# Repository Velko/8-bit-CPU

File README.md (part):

8-bit-CPU
=========

After watching [series of videos][eater-net-8bit] by Ben Eater building an 8-bit computer from scratch,
I was hooked. Various thoughts for improvements and experiments was running through my mind. But first
I have to build one. Improvements will come later. Whom am I kidding? I'll never be able to build an
exact replica, I'll incorporate improvements as I go.

In contrast to Ben, I'm not that crazy about building the whole thing on breadboards. PCBs are fine,
I like them, but building the whole thing on single board takes away the flexibility. So the plan is
to make a small board for each module and connect them together.

I plan to build a prototype module on breadboard, play around with it and then design and make a PCB
for it. It might also be interesting to make the boards little customizable (leave a chip out, create
a solder bridge, use shorter connector) so that they can be re-used for different purposes.

Of course, some parts of it might stay on a breadboard forever, or I might choose to create PCBs for
those as well. I don't know, time will tell. But the main idea is that it should be possible to swap
out PCBs for breadboards and vice versa.

Key differences from Ben's version
==================================

256 bytes of memory
-------------------

I felt that 16 bytes of total memory might be too tight, went for 8-bit addressing and 256 bytes
of memory straight from the beginning. "Real" 32 KiB SRAM chip is used, with remaining higher address
lines tied to ground. Expanding to 256 bytes does not introduce more complexity, I think that it even
made things easier. The emulated version has (and is able to use) 64KiB of memory, hardware version
has not catched up with it yet.

ROM and bootloader mode
-----------------------

I was not in the mood for _any_ DIP switch toggling for program entry, so I added an EEPROM instead.
Still I did not want to go full Harvard architecture with separate program and data memories, so
there's bootloader mode instead.

To enable it, RAM's Chip Enable is connected together with Write Enable, while ROM's Chip Enable is
connected with Output Enable of the RAM. What happens is that all reads comes from ROM and all writes
goes into RAM.

I have bootloader code in the beginning of the program that copies contents of all 256 bytes into RAM
and then patches itself (in RAM) to be skipped. It is nice to have more memory, since in original
version there are only 16 bytes total, but I can afford to _waste_ similar amount on bootloader.

In _run mode_ ROM's Chip Enable is tied to disabled state permanently, while RAM is permanently enabled.

4 flags
-------

In addition to Z and C flags, there are Negative and oVerflow flags. Took an inspiration from
[AVR Instruction Set Manual][avr-instructions], on how to implement various branching instructions.
N and V flags are required for some. N bit is just a copy of 7-th bit of the result. oVerflow indicates
that the sign bit "overflowed" as a result of addition/subtraction. In short it can be defined as:
*If sign bits of both addition operands are equal, but sign bit of the result is different, the overflow
occured.*

C flag got an additional update to act as a Borrow bit in subtraction. It behaves same way as in
Z80 / AVR / x86 processors. In subtraction the meaning of C is opposite from 6502 or Ben's version,
I find this more intuitive.

256 opcodes
-----------

As memory was expanded to 256 bytes, it was not possible to encode opcode and address in single byte
anymore. Instructions may require multiple bytes anyway now. Instruction Register loads 8-bit opcode and
extra arguments are fetched from RAM when needed, there's room for 256 opcodes.

However, number of opcodes is also limited by capacity of control EEPROMs. 8 bits for opcode + 4 bits
for flags + 3 bits for instruction step = 15 address lines. This calls for 32K EEPROM - 28C256. They
felt a little pricey when I ordered parts and I was not completely sure if I'll really need them. For
now I only have 28C64 chips, limiting number of opcodes to 64. It is still 4 times more than in Ben's
version.

There are plans to support "extended" opcodes (up to 512, or even more, if required). Planning to switch
to SST39SF010A chips for microcode ROMs. These have more capacity (and address lines) and are a bit
cheaper as well.

Modular ALU
-----------

Currently there are 2 ALU modules: Add/Subtract (with or without carry/borrow),
and AND/OR. 2 more modules are about to come - XOR/NOT, Shift/Nibble-swap.

Flags register as an independent entity
---------------------------------------

Zero flag's calculation takes input from the Bus, instead of being embedded in ALU module. This allows
to add additional ALU modules and keep just one instance of Z calculation circuitry. Additionally, it
is possible to calculate flags for anything on the Bus, for example - while loading byte from memory.
There's additional function for flags register to be sent and loaded from bus directly. Currently
there is no use for that, but it may become handy if flags need to be saved and restored for some reason
(perhaps, to implement interrupts).

Double-latching registers
-------------------------

One of the main sources of instability in Ben's design is that registers' "tap outputs" (ones that
connects registers to ALU, RAM or Control Logic) change immediately when new value is latched.
This is especially important with Flags and Instruction Register, as it creates the infamous
"EEPROM noise" on the rising clock edge, when it can cause unexpected effects. It might not be such
an issue for general-purpose registers or MAR, but it is better that everything holds steady while
the clock line is high.

The double-latching technique adds additional D flip-flops between register's primary ones and its
"tap output". These additional flip-flops are configured to latch on the inverted clock, therefore
output stays unchanged until the falling edge.

Dual-output registers
---------------------

General purpose registers got dual 3-state "tap outputs". Instead of ALU inputs being hardwired to
registers A and B, now (with appropriate control signals) it is possible to connect them differently,
for example do A + A directly. It also allows additional registers (C and D), that could be used
with ALU directly. Currently this feature is not used and control lines are wired for steady "on",
but the potential is there.

Quarter-clock
-------------

One of the sources of instability in Ben's version is RC-circuit used as an edge detector in RAM
module. A common technique is to isolate the circuit using extra logic gates, so that it does not
send spikes back in clock line. I, however, decided to eliminate the need for edge detection
completely. The thing with RAM is that it will keep loading the value all the time while Write Enable
line is enabled. If inputs change, the last value will be stored, which may not be one we want if
Write Enable is disabled on same moment as other control lines starts to change. Ben solved it using
edge detector circuit, I went in another direction and introduced a "dead time" between moment when
primary clock line goes low and inverted clock rises.

Added a counter (could have been anything that can divide the frequency) and few NOR gates on the
*clock module* I generate two 25% duty-cycle clock signals, that are offset by half of the cycle. It
looks like this:

Part of the cycle when both clocks are low ensures that RAM's Write Enable is not active when control
lines or bus changes.

While it is required only by RAM module, I see no downsides for using it globally (it might be an issue
at high clock frequencies, though). Also, now other un-clocked parts (e.g. 193 counter for Stack Pointer)
can be introduced without worries.

Muxed control lines
-------------------

A great way to save bits in Control EEPROMs is to add demultiplexers, which activates just a single line
from several. For example, by using 74*138 demultiplexer one can expand 3 bits to 7 control lines
(technically - to 8, but you need to reserve one as "unused"). Currently there are 2 demultiplexers
used - for OUT and for LOAD lines. For OUT it also prevents "invalid" conditions, such as multiple
modules trying to output value on the bus.

While, in theory, there might be need to load same value into multiple modules simultaneously, I've
not yet encountered one, and I'm happy to live with that limitation.

No MAR, separate Address Bus
----------------------------

While trying to adjust the architecture for 16-bit memory space, I found out that having a single
Main Bus and Memory Address Register comes with performance penalty, as all address transfers takes
more cycles.

After some experimentation I found out that the most optimal solution is to remove the MAR entirely
and have a separate 16-bit Address Bus, connected directly to the RAM chip(s).

Now, for example, Progam Counter can put an address on this bus, and the data is available to be sent on the
Main Bus.

Additionally, I re-designed PC in a way, that it can output the "old" value on the Address Bus, and
increment itself simultaneously. As a result, I can reduce the fetch stage of each instruction to just
single cycle.

There are some situations (like JMP instruction), when data should be exchanged between Address and
Main buses. There's a pair of special Transfer Registers, that allows to transfer low or high bytes
between the buses.

Arduino + Python test module
----------------------------

It started with hooking up an Arduino (on its own at first, then expanded output with 595 shift registers,
expanded even more with 139 demultiplexers and finally added 165 for expanded input) and writing some
sketches to verify if modules work as expected. Soon I realized that the environment is a bit limited
and while it can prove that everything works, it is not very helpful for diagnostics.

Reducing the functions of Arduino to "set control lines", "put to bus", "read from bus", "read flags",
"pulse a clock", etc. and implementing higher level logic in Python, makes it more flexible and quicker
to develop. Wrote a "client" that uses interactive input for diagnostics.

Started to implement Python functions that acts as an assembly instructions - for example: add(A, B)
switches all control lines and issues clock ticks as needed for the addition operation. Basically -
implemented microcode in Python. Later, with refactoring it became my main microcode definition and
is used as primary source for microcode EEPROM contents.

Using the instruction-like functions and [pytest][pytest] framework wrote a quite thorough test suite.
It can check couple hundred scenarios in just few seconds and point out if something does not work as
expected. It has already saved me several times, when I did some rewiring.

At the moment the test module is swapped out for "real" EEPROM-based Control Logic, but I'll definitely
find a way to use both of them in parallel, as it is too useful to be retired.

Programmed using CustomAsm
--------------------------

There was Python-based "assembler" at first, but in the end I adopted [CustomAsm][customasm] for
machine code generation. There's an utility that takes my microcode definition and exports a file,
describing them for [CustomAsm][customasm]. It takes it from there.

Debugger & IDE
--------------
As the Test module allows great deal of flexibility, I was able to also develop a simple debugger.
It can examine registers, RAM contents, single step. Addition of BRK instruction and corresponding
control line introduced ability to set breakpoints and run the program in full-speed. Unfortunately
it only works with emulator, as current hardware doesn't support both "normal" Control Logic and
Test modules connected simultaneously.

Later I went even further and developed a simple IDE, that allows basic code editing, integrates
with [CustomAsm][customasm] for compilation and has basic debugging functionality. One can single-step,
set breakpoints, examine registers. The IDE is far from polished experience, still it is useful.

Side-projects: EEPROM and Flash writers
---------------------------------------

As side projects, there are 2 boards (Arduino Uno shields), firmware and client utility for
programming DIP-28 and PLCC-32 EEPROMs (AT28C64 and AT28C256), as well as PLCC-32 Multi-Purpose
Flash (SST39SF*).

EEPROM board has additional headers, giving access to address and data pins, allowing the board to
act as a Test module, when connected to the Main Bus and control lines.

File upload and download uses XMODEM protocol, can be used with any terminal emulator. There's also
a (*nix-only) command-line client utility for convenience.

Emulated in Verilog
-------------------

In order to be able to work with the software side of the project, when hardware was not available,
I wrote an in-Arduino emulator, that speaks same protocol as Test module. With time that proved to
be insufficient, as Arduino was still needed, so I ported the C++ code to run on PC. It worked fine,
but was a hand-crafted approximation of the CPU, so I could not really test all "what if" scenarios
I'd like to.

So I decided to build another emulator, using proper hardware description language - [Verilog][verilog].
The idea was that I first make "building blocks" - (hopefully accurate) implementations of 74-series
logic chips, and then connect them together into CPU modules. This way I get a runnable representation
of the thing, how it should be built with real chips.

To provide connectivity with (virtualized) serial port, I built additional [VPI][vpi] module.

Repository index
================

* **.github** - configuration files for GitHub integration, e.g. workflows for GitHub Actions
* **.vscode** - configuration for Visual Studio Code
* **arduino** - Arduino sketches and C++ code, to help test and automate things
    * **bouncyy** - software button debouncer and "rebouncer"
    * **pincontrol** - substitute Control Logic. Controlled via serial link from **pycontrol**
    * **xmprog** - EEPROM/Flash programmer, file upload using XMODEM protocol
* **demo** - demo programs
* **doc** - some (mostly outdated) design thoughts, BOM, etc.
* **emulator** - hardware emulator in Verilog
    * **chips** - Verilog descriptions of (mostly 74xx) chips
    * **cpu-modules** - "wired up" CPU modules
    * **tests** - test benches for chips and modules
    * **vm** - a "virtual machine". Speaks same protocol as **pincontrol**
* **hardware** - hardware schematics, boards, etc.
    * **breadboard** - Fritzig projects for some modules
    * **pcb** - KiCad schematics and boards
        * **alu_back** - backplane board for ALU and GP registers
        * **aunit** - Arithmetic Unit (ALU module for addition and subtraction)
        * **clock** - (unfinished) Clock module
        * **control** - (unfinished) Control Logic
        * **counter** - Program Counter
        * **display_back** - backend board for Output module (7-seg display)
        * **display_front** - frontend board for Output module (7-seg display)
        * **eeprom_burner** - EEPROM writer as Arduino Uno shield
        * **flags** - Flags register
        * **flash_writer** - Arduino Uno shield - writer for SST39SF0*-series Flash chips (chosen EEPROM replacement)
        * **keyboard** - (unfinished) 4x4 keyboard scanner module
        * **lunit** - Logic Unit (ALU module for AND and OR)
        * **modules** - Register, ALU, etc. boards as KiCad footprints (for backplane)
        * **ram** - (unfinished) RAM module
        * **register** - GP register
        * **sunit** - Shift Unit (ALU module for shift and nibble swap)
        * **transfer** - transfer register (between Main Bus and Address Bus)
* **include** - C and .def files for inclusion on other programs
* **misc** - miscellaneous utilities
    * **digits** - an utility to generate binary ROM image for 7-segment display
    * **xmclient** - PC-side client utility for **xmprog**
* **parts** - custom KiCad symbols and footprints for missing components
* **pycontrol** - Python-based control logic, microcode, tests, demo programs, etc.
    * **ide** - a simple PyGTK-based IDE with graphical debugger
    * **libcpu** - main implementation of control logic, microcode
    * **stubs** - MyPy type definitions for packages that lack those
    * **tests** - PyTest scripts, testing (real or emulated) hardware and PyControl itself
    * **tools** - various tools that generates microcode, customasm definitions, execute and debug binaries
* **simulation** - [Logisim][logisim] and [Digital][digital] simulations for tricky logic
* **turbo** - high-performance hardware emulator in Rust
    * **core** - core CPU implementation
    * **peripherals** - implementations of various peripherals, e.g. displays, UART, etc.
    * **bridge** - communication bridge between emulator and clients over UDP
    * **vm** - a "virtual machine", tying it all together

Progress
========

* Created Github project and added few most immediate tasks
* Wrote an introductionary README (this one ;-) )
* Decided on overall design
* Compiled list of modules and parts for first experiments, placed an order with my favorite supplier
* Found Arduino, breadboard and few 7-segment displays at home. Time to practice!
* Built breadboard prototypes for Clock, Register, Counter, Display and EEPROM burner
* Built ALU, complete with upgraded Flags register.
* Wrote some [blog posts][velkoraspi] about the "adventures"
* Arduino-based testing device. Connect the module, run a command and it verifies that module works
  as expected.
* Designed, soldered PCB versions of Register, ALU, Flags and EEPROM programmer
* Reworked testing device - moved most logic to "client" side. Coding in Python is a lot quicker
  than constantly re-flashing the Arduino. Can use unit-test framework, use debugger, quick edits.
* Beginnings of instruction set.
* Soldered 2 more Registers, to be used as MAR and IR
* Built breadboard prototype of RAM module (placed MAR and IR on it), wrote some unittests for it
* Wired both ALU and RAM blocks to Arduino, merged test suites
* Hey, it can calculate and there's memory. That should be enough to do something more complex.
* Developed Sieve of Eratosthenes - calculate prime numbers up to 256. A Python program, which uses
  assembly-like functions to manipulate the ALU and RAM modules. All variables/arrays required for
  algorithm are stored in the RAM. The control flow reads its input only from Flags register. This
  should be almost 1:1 translatable to assembly / machine code
* Play around with Python AST visitor to automatically "flatten" the program and add necessary labels
  and jumps to replace Python's while/if/continue/break control flow. When executed, this program generates
  machine code.
* Built a dedicated "debug control" board using Nano, shift registers and demultiplexers
* Connected Program Counter and "read-back" from IR into Arduino. Should be able to "run" programs from
  memory
* Developed a Python-side instruction interpreter, which uses input from IR and flags to select and
  execute appropriate microcode steps. Now it really runs machine code, albeit using weird (and very slow)
  control logic
* Developed utility that dumps current microcode (Python) definitions to C arrays.
* Wrote an Arduino-side instruction interpreter that uses the C microcode arrays and input from IR and
  Flags. Now can run programs without Python-side involvement
* Added an EEPROM in RAM module. Added a bootloader code in the Prime Sieve demo. The bootloader copies
  contents from ROM into RAM and patches itself to be skipped next time
* Implemented a "quarter clock" on the Clock board. Now it produces two 25% duty-cycle clock signals,
  instead of two 50% ones. This should eliminate need for edge-detection circuitry in RAM module.
* Built an EEPROM-based control board. Flashed microcode into ROMs.
* Swapped out Arduino-based control board with EEPROM-based one. A very error-prone operation, I must admit.
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
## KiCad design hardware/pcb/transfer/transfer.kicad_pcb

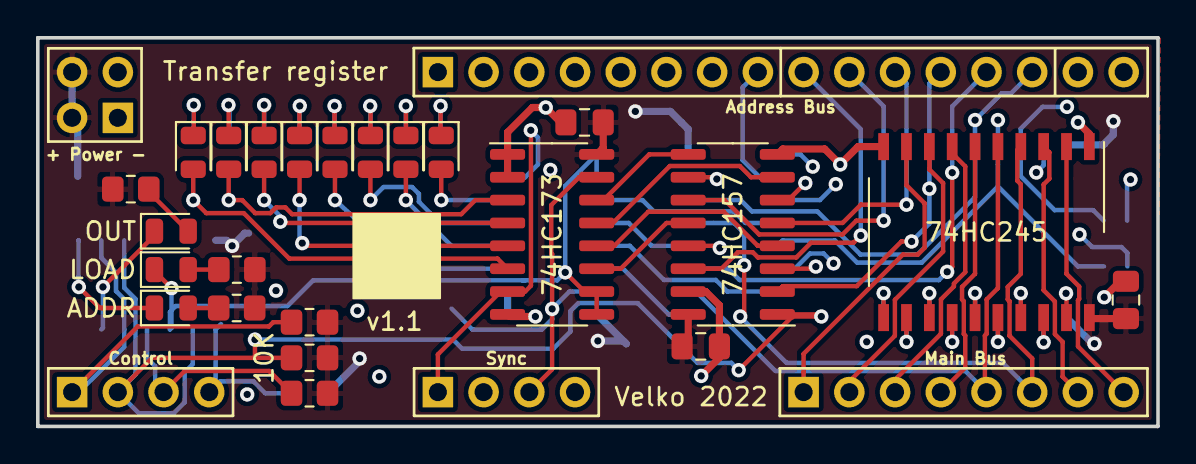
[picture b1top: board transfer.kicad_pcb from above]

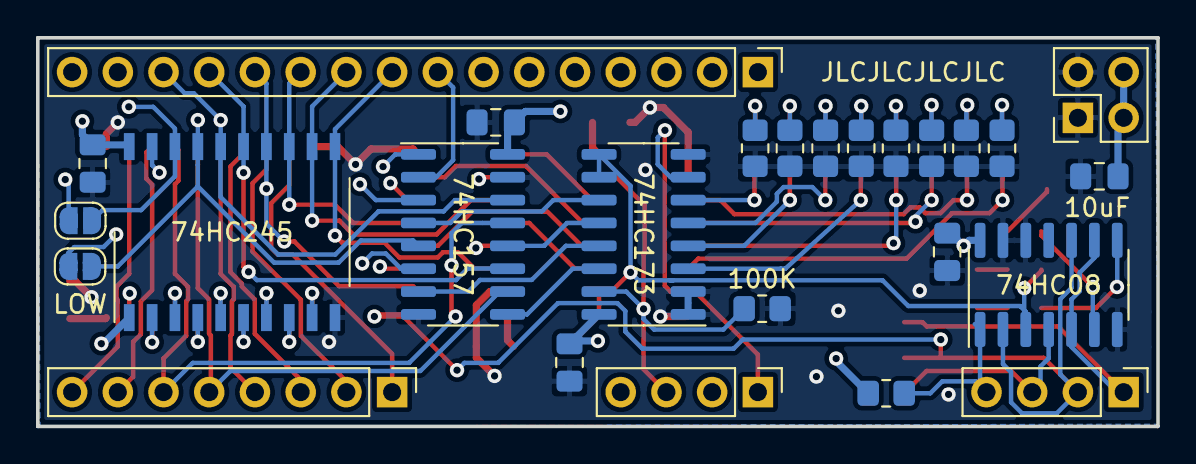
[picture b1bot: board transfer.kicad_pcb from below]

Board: 4 copper layers, 62.2 x 21.6 mm, 49 parts (26 on the bottom side), 56 nets.

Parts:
C1, C2, C3, C4, C5, C6, C8: 100nF; C_0805_2012Metric_Pad1.18x1.45mm_HandSolder
C7: 10uF; C_0805_2012Metric_Pad1.18x1.45mm_HandSolder
D1, D2, D3, D4, D5, D6, D7, D8: LED; LED_0805_2012Metric
D9: LOAD; LED_0805_2012Metric
D10: OUT; LED_0805_2012Metric
D11: ADDR; LED_0805_2012Metric
J2: Control; PinHeader_1x04_P2.54mm_Vertical
J3: Sync; PinHeader_1x04_P2.54mm_Vertical
J4: + Power -; PinHeader_2x02_P2.54mm_Vertical
J5: Address Bus; PinHeader_1x16_P2.54mm_Vertical
J6: Main Bus; PinHeader_1x08_P2.54mm_Vertical
JP1: LOW; SolderJumper-2_P1.3mm_Open_RoundedPad1.0x1.5mm
JP2: L; SolderJumper-2_P1.3mm_Open_RoundedPad1.0x1.5mm
R1, R2, R3, R4, R5, R6, R7, R8, R9, R10, R11: 330; R_0805_2012Metric_Pad1.20x1.40mm_HandSolder
R12, R13, R14, R15: 10K; R_0805_2012Metric_Pad1.20x1.40mm_HandSolder
R16: 100K; R_0805_2012Metric_Pad1.20x1.40mm_HandSolder
U1, U4: 74HC173; SOIC-16_3.9x9.9mm_P1.27mm
U2, U5: 74HC157; SOIC-16_3.9x9.9mm_P1.27mm
U3, U9: 74HC245; SO-20_12.8x7.5mm_P1.27mm
U6: 74HC08; SOIC-14_3.9x8.7mm_P1.27mm

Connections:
ABUS0: J5.8, JP1.1, U2.2, U3.18
ABUS1: J5.7, JP2.1, U2.5, U3.17
ABUS2: J5.6, J5.14, U2.14, U3.16
ABUS3: J5.5, J5.13, U2.11, U3.15
ABUS4: J5.4, J5.12, U3.14, U5.2
ABUS5: J5.3, J5.11, U3.13, U5.5
ABUS6: J5.2, J5.10, U3.12, U5.11
ABUS7: J5.1, J5.9, U3.11, U5.14
ALOAD: J2.2, R13.2, U2.1, U5.1, U6.2, U6.10
AOUT: J2.1, R12.2, U3.19, U6.5, U6.9
CLK: J3.1, U1.7, U4.7
GND: C1.2, C2.2, C3.2, C4.2, C5.2, C6.2, C7.2, C8.2, J4.1, J4.2, R1.1, R2.1, R3.1, R4.1, R5.1, R6.1, R7.1, R8.1, R16.1, U1.1, U1.2, U1.8, U2.8, U2.15, U3.10, U4.1, U4.2, U4.8, U5.8, U5.15, U6.7, U6.12, U6.13, U9.1, U9.10
LD0: U1.11, U2.4
LD1: U1.13, U2.7
LD2: U1.12, U2.12
LD3: U1.14, U2.9
LD4: U4.12, U5.4
LD5: U4.13, U5.7
LD6: U4.14, U5.9
LD7: U4.11, U5.12
LOAD: D9.1, U1.9, U1.10, U4.9, U4.10, U6.3
MBUS0: J6.8, U2.3, U9.2
MBUS1: J6.7, U2.6, U9.3
MBUS2: J6.6, U2.13, U9.4
MBUS3: J6.5, U2.10, U9.5
MBUS4: J6.4, U5.3, U9.6
MBUS5: J6.3, U5.6, U9.7
MBUS6: J6.2, U5.10, U9.8
MBUS7: J6.1, U5.13, U9.9
MLOAD: J2.4, R15.2, U6.1
MOUT: J2.3, R14.2, U6.4, U9.19
unnamed: D1.1, R1.2
unnamed: D2.1, R2.2
unnamed: D3.1, R3.2
unnamed: D4.1, R4.2
unnamed: D5.1, R5.2
unnamed: D6.1, R6.2
unnamed: D7.1, R7.2
unnamed: D8.1, R8.2
unnamed: D9.2, R9.2
unnamed: D10.2, R10.2
unnamed: D11.1, U6.8
unnamed: D11.2, R11.2
unnamed: J5.15, JP2.2
unnamed: J5.16, JP1.2
OUT: D10.1, U6.6
OUT0: D1.2, U1.6, U3.2, U9.18
OUT1: D2.2, U1.4, U3.3, U9.17
OUT2: D3.2, U1.5, U3.4, U9.16
OUT3: D4.2, U1.3, U3.5, U9.15
OUT4: D5.2, U3.6, U4.5, U9.14
OUT5: D6.2, U3.7, U4.4, U9.13
OUT6: D7.2, U3.8, U4.3, U9.12
OUT7: D8.2, U3.9, U4.6, U9.11
RST: J3.3, R16.2, U1.15, U4.15
VCC: C1.1, C2.1, C3.1, C4.1, C5.1, C6.1, C7.1, C8.1, J4.3, J4.4, R9.1, R10.1, R11.1, R12.1, R13.1, R14.1, R15.1, U1.16, U2.16, U3.1, U3.20, U4.16, U5.16, U6.14, U9.20

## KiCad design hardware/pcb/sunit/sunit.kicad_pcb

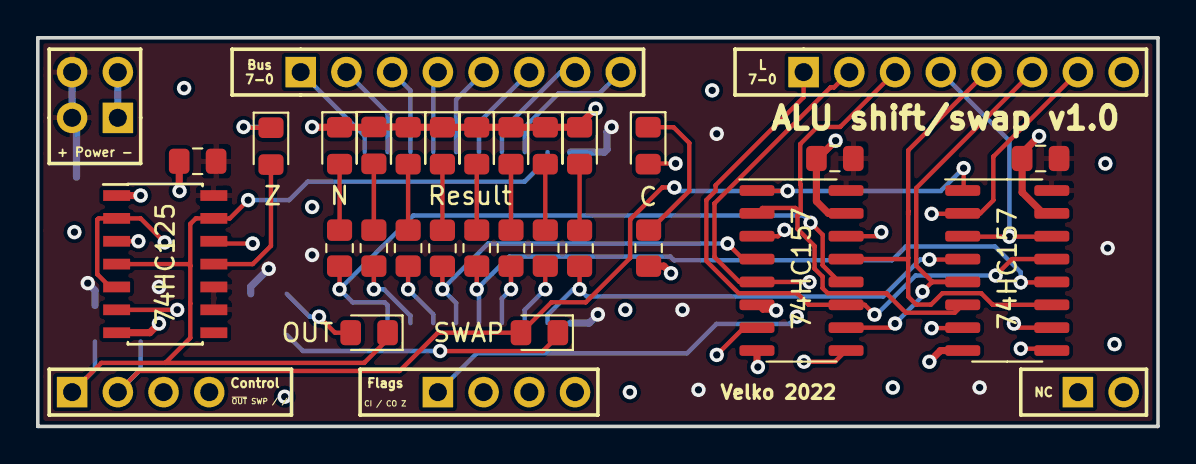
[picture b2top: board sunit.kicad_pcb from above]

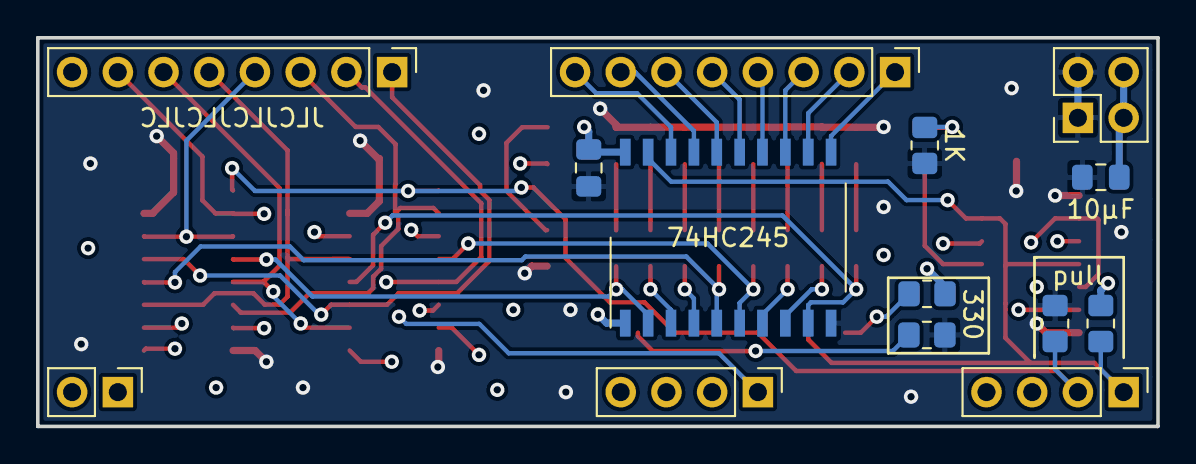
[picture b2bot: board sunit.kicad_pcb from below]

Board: 4 copper layers, 62.2 x 21.6 mm, 41 parts (14 on the bottom side), 45 nets.

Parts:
C1: 10μF; C_0805_2012Metric_Pad1.15x1.40mm_HandSolder
C2, C3, C6, C8: 100nF; C_0805_2012Metric_Pad1.15x1.40mm_HandSolder
D1: 0; LED_0805_2012Metric_Pad1.15x1.40mm_HandSolder
D2: 1; LED_0805_2012Metric_Pad1.15x1.40mm_HandSolder
D3: 2; LED_0805_2012Metric_Pad1.15x1.40mm_HandSolder
D4: Result; LED_0805_2012Metric_Pad1.15x1.40mm_HandSolder
D5: 4; LED_0805_2012Metric_Pad1.15x1.40mm_HandSolder
D6: 5; LED_0805_2012Metric_Pad1.15x1.40mm_HandSolder
D7: 6; LED_0805_2012Metric_Pad1.15x1.40mm_HandSolder
D8: N; LED_0805_2012Metric_Pad1.15x1.40mm_HandSolder
D9: OUT; LED_0805_2012Metric_Pad1.15x1.40mm_HandSolder
D10: SWAP; LED_0805_2012Metric_Pad1.15x1.40mm_HandSolder
D11: Z; LED_0805_2012Metric_Pad1.15x1.40mm_HandSolder
D12: C; LED_0805_2012Metric_Pad1.15x1.40mm_HandSolder
J1: Power; PinHeader_2x02_P2.54mm_Vertical
J2: Control; PinHeader_1x04_P2.54mm_Vertical
J3: BUS; PinHeader_1x08_P2.54mm_Vertical
J4: Input A; PinHeader_1x08_P2.54mm_Vertical
J5: Flags; PinHeader_1x04_P2.54mm_Vertical
J6: Input B; PinHeader_1x02_P2.54mm_Vertical
R1, R2, R3, R4, R5, R6, R7, R8, R9, R10, R14: 330; R_0805_2012Metric_Pad1.20x1.40mm_HandSolder
R11: 1K; R_0805_2012Metric_Pad1.20x1.40mm_HandSolder
R12, R13: 10K; R_0805_2012Metric_Pad1.20x1.40mm_HandSolder
U5: 74HC125; SOIC-14_3.9x8.7mm_P1.27mm
U6, U7: 74HC157; SOIC-16_3.9x9.9mm_P1.27mm
U8: 74HC245; SO-20_12.8x7.5mm_P1.27mm

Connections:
A0: J4.8, U5.2, U5.5, U6.3
A1: J4.7, U6.6, U7.2
A2: J4.6, U6.10, U7.5
A3: J4.5, U6.13, U7.11
A4: J4.4, U7.3, U7.14
A5: J4.3, U6.2, U7.6
A6: J4.2, U6.5, U7.10
A7: J4.1, U6.11, U7.13
BUS0: J3.8, U8.18
BUS1: J3.7, U8.17
BUS2: J3.6, U8.16
BUS3: J3.5, U8.15
BUS4: J3.4, U8.14
BUS5: J3.3, U8.13
BUS6: J3.2, U8.12
BUS7: J3.1, U8.11
CIN: J5.1, U6.14
COUT: J5.3, U5.6
GND: C1.2, C2.2, C3.2, C6.2, C8.2, D1.1, D2.1, D3.1, D4.1, D5.1, D6.1, D7.1, D8.1, J1.1, J1.2, R10.1, R11.1, R13.1, R14.1, U5.1, U5.7, U6.8, U6.15, U7.8, U7.15, U8.10
unnamed: D1.2, R1.1
unnamed: D2.2, R2.1
unnamed: D3.2, R3.1
unnamed: D4.2, R4.1
unnamed: D5.2, R5.1
unnamed: D6.2, R6.1
unnamed: D7.2, R7.1
unnamed: D8.2, R8.1
unnamed: D9.2, R9.2
unnamed: D10.1, R10.2
unnamed: D11.1, R11.2
unnamed: D11.2, U5.11
unnamed: D12.1, R14.2
unnamed: D12.2, U5.3
RES0: R1.2, U7.4, U8.2
RES1: R2.2, U7.7, U8.3
RES2: R3.2, U7.9, U8.4
RES3: R4.2, U7.12, U8.5
RES4: R5.2, U6.4, U8.6
RES5: R6.2, U6.7, U8.7
RES6: R7.2, U6.9, U8.8
RES7: R8.2, U6.12, U8.9
SH_SWP: D10.2, J2.2, R13.2, U6.1, U7.1
VCC: C1.1, C2.1, C3.1, C6.1, C8.1, J1.3, J1.4, R9.1, R12.2, U5.9, U5.10, U5.14, U6.16, U7.16, U8.1, U8.20
ZIN: J5.4, U5.12
~OUT~: D9.1, J2.1, R12.1, U5.4, U5.13, U8.19

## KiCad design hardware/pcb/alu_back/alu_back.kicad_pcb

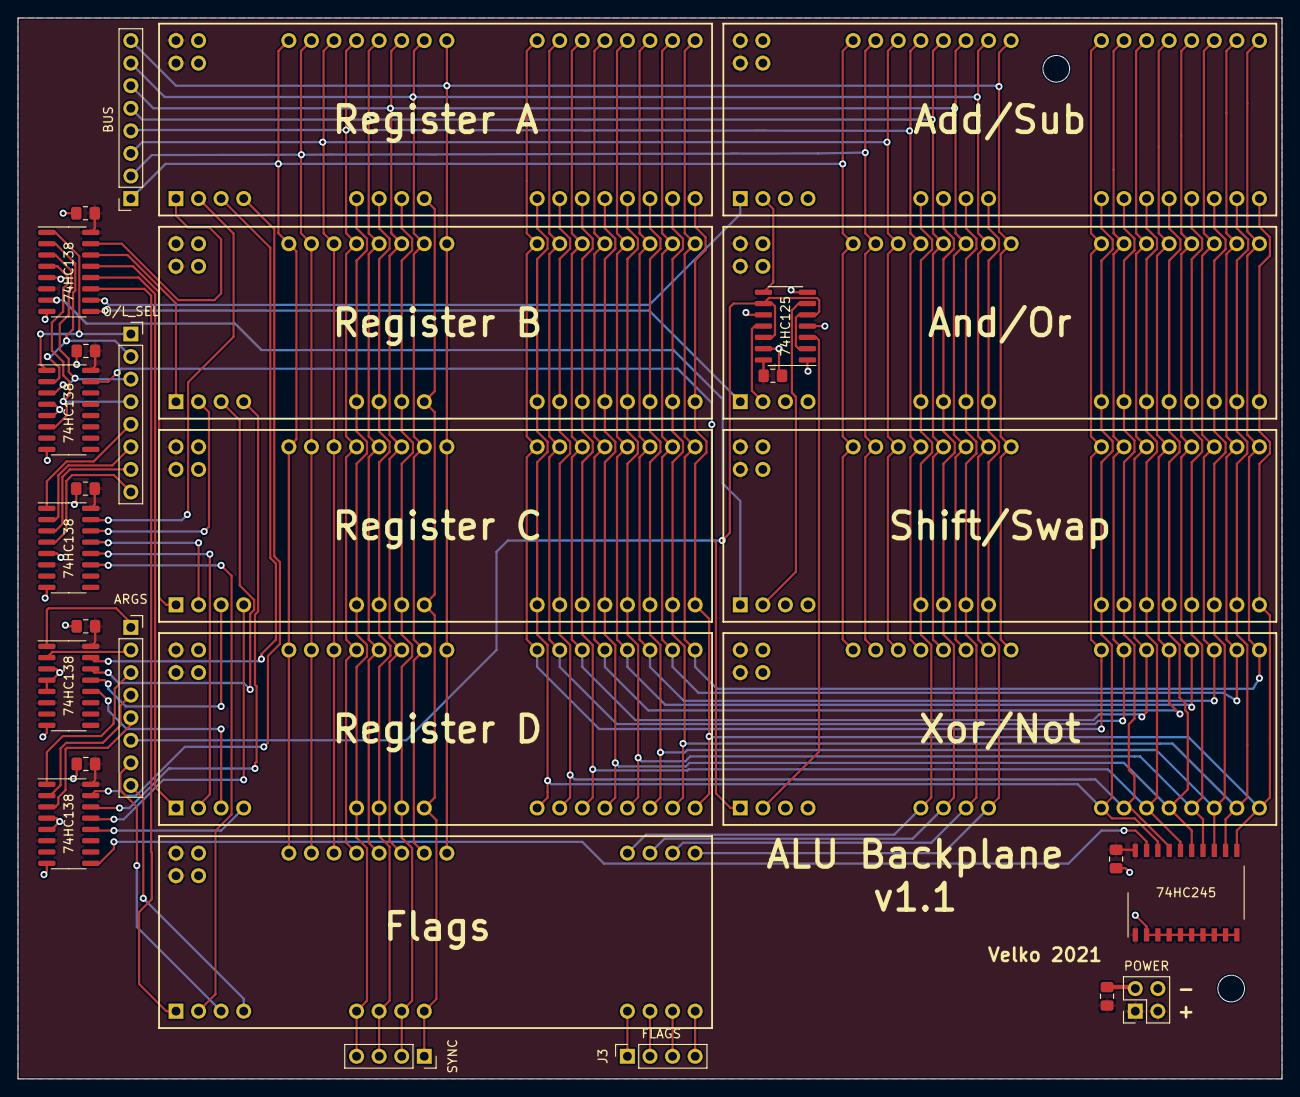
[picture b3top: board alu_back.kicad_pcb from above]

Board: 2 copper layers, 142.2 x 119.4 mm, 35 parts (0 on the bottom side), 81 nets.

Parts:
C1: 10uF; C_0805_2012Metric_Pad1.18x1.45mm_HandSolder
C2, C3, C4, C5, C6, C7, C8: 100nF; C_0805_2012Metric_Pad1.18x1.45mm_HandSolder
H1, H2, H3, H4, H5: MountingHole; MountingHole_3mm
J1: SYNC; PinSocket_1x04_P2.54mm_Vertical
J2: BUS; PinSocket_1x08_P2.54mm_Vertical
J3: FLAGS; PinSocket_1x04_P2.54mm_Vertical
J4: O/L_SEL; PinSocket_1x08_P2.54mm_Vertical
J7: ARGS; PinSocket_1x08_P2.54mm_Vertical
J8: POWER; PinSocket_2x02_P2.54mm_Vertical
U1: Register A; Register_board
U2: Register B; Register_board
U3: Register C; Register_board
U4: Register D; Register_board
U5: Add/Sub; Register_board
U6: And/Or; Register_board
U7: Xor/Not; Register_board
U8: Shift/Swap; Register_board
U9: Flags; Flags_board
U10: 74HC125; SOIC-14_3.9x8.7mm_P1.27mm
U11: 74HC245; SO-20_12.8x7.5mm_P1.27mm
U12, U13, U14, U15, U16: 74HC138; SOIC-16_3.9x9.9mm_P1.27mm

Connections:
/BUS0: J2.8, U1.25, U2.25, U3.25, U4.25, U5.25, U6.25, U7.25, U8.25, U9.17
/BUS1: J2.7, U1.26, U2.26, U3.26, U4.26, U5.26, U6.26, U7.26, U8.26, U9.18
/BUS2: J2.6, U1.27, U2.27, U3.27, U4.27, U5.27, U6.27, U7.27, U8.27, U9.19
/BUS3: J2.5, U1.28, U2.28, U3.28, U4.28, U5.28, U6.28, U7.28, U8.28, U9.20
/BUS4: J2.4, U1.29, U2.29, U3.29, U4.29, U5.29, U6.29, U7.29, U8.29, U9.21
/BUS5: J2.3, U1.30, U2.30, U3.30, U4.30, U5.30, U6.30, U7.30, U8.30, U9.22
/BUS6: J2.2, U1.31, U2.31, U3.31, U4.31, U5.31, U6.31, U7.31, U8.31, U9.23
/BUS7: J2.1, U1.32, U2.32, U3.32, U4.32, U5.32, U6.32, U7.32, U8.32, U9.24
/CAF: U5.7, U6.7, U7.7, U8.7, U9.14
/CFA: U5.5, U6.5, U7.5, U8.5, U9.16
/L0: U1.17, U2.17, U3.17, U4.17, U5.17, U6.17, U7.17, U8.17
/L1: U1.18, U2.18, U3.18, U4.18, U5.18, U6.18, U7.18, U8.18
/L2: U1.19, U2.19, U3.19, U4.19, U5.19, U6.19, U7.19, U8.19
/L3: U1.20, U2.20, U3.20, U4.20, U5.20, U6.20, U7.20, U8.20
/L4: U1.21, U2.21, U3.21, U4.21, U5.21, U6.21, U7.21, U8.21
/L5: U1.22, U2.22, U3.22, U4.22, U5.22, U6.22, U7.22, U8.22
/L6: U1.23, U2.23, U3.23, U4.23, U5.23, U6.23, U7.23, U8.23
/L7: U1.24, U2.24, U3.24, U4.24, U5.24, U6.24, U7.24, U8.24
/R0: U1.16, U2.16, U3.16, U4.16, U5.16, U6.16, U7.16, U8.16, U11.11
/R1: U1.15, U2.15, U3.15, U4.15, U5.15, U6.15, U7.15, U8.15, U11.12
/R2: U1.14, U2.14, U3.14, U4.14, U5.14, U6.14, U7.14, U8.14, U11.13
/R3: U1.13, U2.13, U3.13, U4.13, U5.13, U6.13, U7.13, U8.13, U11.14
/R4: U1.12, U2.12, U3.12, U4.12, U5.12, U6.12, U7.12, U8.12, U11.15
/R5: U1.11, U2.11, U3.11, U4.11, U5.11, U6.11, U7.11, U8.11, U11.16
/R6: U1.10, U2.10, U3.10, U4.10, U5.10, U6.10, U7.10, U8.10, U11.17
/R7: U1.9, U2.9, U3.9, U4.9, U5.9, U6.9, U7.9, U8.9, U11.18
/V: U5.6, U6.6, U7.6, U8.6, U9.15
/Z: U5.8, U6.8, U7.8, U8.8, U9.13
ALT: J7.6, U10.2, U10.5, U10.9, U10.12
ALT_AO: U6.2, U10.11
ALT_AS: U5.2, U10.8
ALT_S: U8.2, U10.6
ALT_XN: U7.2, U10.3
ARG_AL: U1.3, U12.15
ARG_AR: U1.4, U13.15
ARG_BL: U2.3, U12.14
ARG_BR: U2.4, U13.14
ARG_CL: U3.3, U12.13
ARG_CR: U3.4, U13.13
ARG_DL: U4.3, U12.12
ARG_DR: U4.4, U13.12
ARG_L0: J7.1, U12.1
ARG_L1: J7.2, U12.2
ARG_R0: J7.3, U13.1
ARG_R1: J7.4, U13.2
ARG_R2: J7.5, U13.3
ARG_ZR: U11.19, U13.9
CARRY: J7.8, U9.4
CLK: J1.4, U1.5, U2.5, U3.5, U4.5, U9.5
F_CALC: J7.7, U9.3
GND: C1.2, C2.2, C3.2, C4.2, C5.2, C6.2, C7.2, C8.2, J8.3, J8.4, U1.33, U1.35, U2.33, U2.35, U3.33, U3.35, U4.33, U4.35, U5.33, U5.35, U6.33, U6.35, U7.33, U7.35, U8.33, U8.35, U9.25, U9.27, U10.1, U10.4, U10.7, U10.10, U10.13, U11.2, U11.3, U11.4, U11.5, U11.6, U11.7, U11.8, U11.9, U11.10, U12.3, U12.4, U12.5, U12.8, U13.4, U13.5, U13.8, U14.5, U14.8, U15.5, U15.8, U16.4, U16.5, U16.8
LOAD_A: U1.2, U15.15
LOAD_B: U2.2, U15.14
LOAD_C: U3.2, U15.13
LOAD_D: U4.2, U15.12
LOAD_F: U9.2, U15.11
LOAD_SEL0: J4.5, U15.1
LOAD_SEL1: J4.6, U15.2
LOAD_SEL2: J4.7, U15.3
LOAD_SEL3: J4.8, U15.4
unnamed: J3.1, U9.9
unnamed: J3.2, U9.10
unnamed: J3.3, U9.11
unnamed: J3.4, U9.12
OUT_A: U1.1, U14.15
OUT_AO: U6.1, U14.9
OUT_AS: U5.1, U14.10
OUT_B: U2.1, U14.14
OUT_C: U3.1, U14.13
OUT_D: U4.1, U14.12
OUT_F: U9.1, U14.11
OUT_S: U8.1, U14.7
OUT_SEL0: J4.1, U14.1, U16.1
OUT_SEL1: J4.2, U14.2, U16.2
OUT_SEL2: J4.3, U14.3, U16.3
OUT_SEL3: J4.4, U14.4, U16.6
OUT_XN: U7.1, U16.15
RESET: J1.2, U1.7, U2.7, U3.7, U4.7, U9.7
VCC: C1.1, C2.1, C3.1, C4.1, C5.1, C6.1, C7.1, C8.1, J8.1, J8.2, U1.34, U1.36, U2.34, U2.36, U3.34, U3.36, U4.34, U4.36, U5.34, U5.36, U6.34, U6.36, U7.34, U7.36, U8.34, U8.36, U9.26, U9.28, U10.14, U11.1, U11.20, U12.6, U12.16, U13.6, U13.16, U14.6, U14.16, U15.6, U15.16, U16.16
~CLK~: J1.3, U1.6, U2.6, U3.6, U4.6, U9.6
~RESET~: J1.1, U1.8, U2.8, U3.8, U4.8, U9.8

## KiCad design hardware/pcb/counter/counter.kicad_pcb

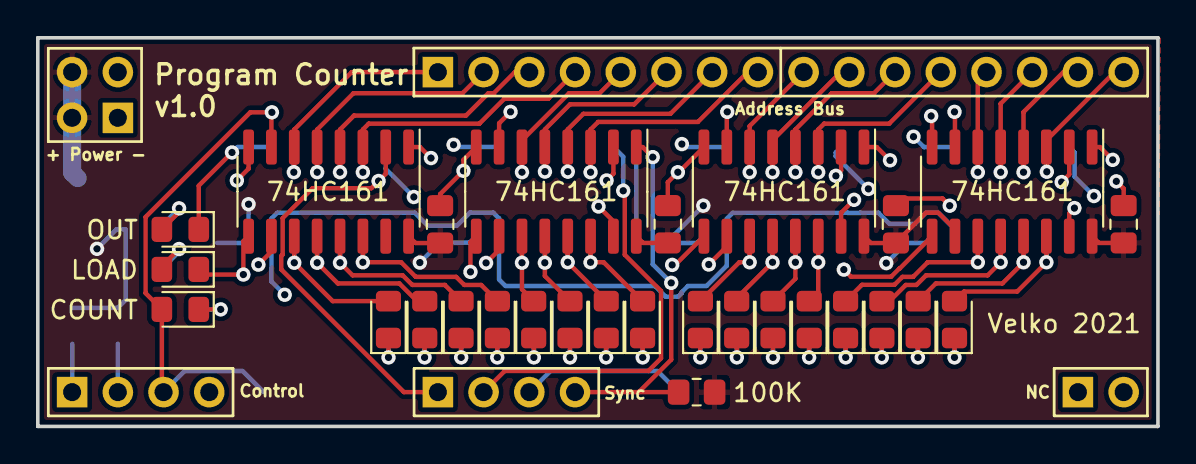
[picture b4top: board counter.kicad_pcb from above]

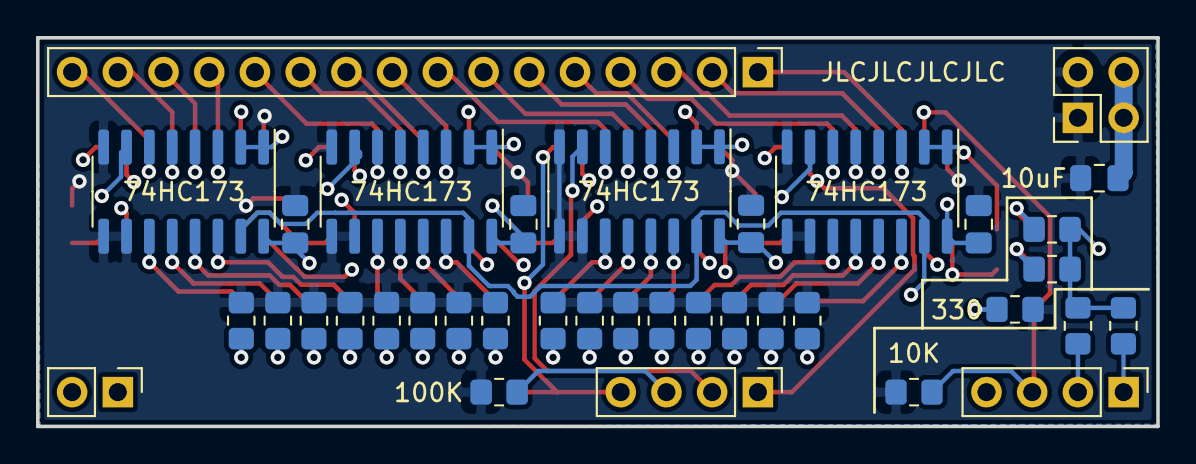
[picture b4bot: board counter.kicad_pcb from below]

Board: 4 copper layers, 62.2 x 21.6 mm, 65 parts (37 on the bottom side), 63 nets.

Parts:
C1, C2, C3, C4, C5, C6, C7, C8: 100nF; C_0805_2012Metric_Pad1.18x1.45mm_HandSolder
C9: 10uF; C_0805_2012Metric_Pad1.18x1.45mm_HandSolder
D1, D2, D3, D4, D5, D6, D7, D8, D9, D10, D11, D12, D13, D14, D15, D16: LED; LED_0805_2012Metric_Pad1.15x1.40mm_HandSolder
D17: OUT; LED_0805_2012Metric_Pad1.15x1.40mm_HandSolder
D18: LOAD; LED_0805_2012Metric_Pad1.15x1.40mm_HandSolder
D19: COUNT; LED_0805_2012Metric_Pad1.15x1.40mm_HandSolder
J2: Control; PinHeader_1x04_P2.54mm_Vertical
J3: Sync; PinHeader_1x04_P2.54mm_Vertical
J4: + Power -; PinHeader_2x02_P2.54mm_Vertical
J5: Address Bus; PinHeader_1x16_P2.54mm_Vertical
J6: NC; PinHeader_1x02_P2.54mm_Vertical
R1, R2, R3, R4, R5, R6, R7, R8, R9, R10, R11, R12, R13, R14, R15, R16, R17, R19, R21: 330; R_0805_2012Metric_Pad1.20x1.40mm_HandSolder
R18, R20, R22: 10K; R_0805_2012Metric_Pad1.20x1.40mm_HandSolder
R23, R24: 100K; R_0805_2012Metric_Pad1.20x1.40mm_HandSolder
U1, U5, U7, U9: 74HC161; SOIC-16_3.9x9.9mm_P1.27mm
U2, U6, U8, U10: 74HC173; SOIC-16_3.9x9.9mm_P1.27mm

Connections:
ABUS0: J5.16, U1.3, U2.6
ABUS1: J5.15, U1.4, U2.5
ABUS2: J5.14, U1.5, U2.4
ABUS3: J5.13, U1.6, U2.3
ABUS4: J5.12, U5.3, U6.6
ABUS5: J5.11, U5.4, U6.5
ABUS6: J5.10, U5.5, U6.4
ABUS7: J5.9, U5.6, U6.3
ABUS8: J5.8, U7.3, U8.6
ABUS9: J5.7, U7.4, U8.5
ABUS10: J5.6, U7.5, U8.4
ABUS11: J5.5, U7.6, U8.3
ABUS12: J5.4, U9.3, U10.6
ABUS13: J5.3, U9.4, U10.5
ABUS14: J5.2, U9.5, U10.4
ABUS15: J5.1, U9.6, U10.3
AOUT: D17.1, J2.1, R18.1, U2.1, U2.2, U6.1, U6.2, U8.1, U8.2, U10.1, U10.2
CLK: J3.1, U1.2, U5.2, U7.2, U9.2
GND: C1.2, C2.2, C3.2, C4.2, C5.2, C6.2, C7.2, C8.2, C9.2, J4.1, J4.2, R1.1, R2.1, R3.1, R4.1, R5.1, R6.1, R7.1, R8.1, R9.1, R10.1, R11.1, R12.1, R13.1, R14.1, R15.1, R16.1, R21.1, R22.2, R24.1, U1.8, U2.8, U2.9, U2.10, U5.8, U6.8, U6.9, U6.10, U7.8, U8.8, U8.9, U8.10, U9.8, U10.8, U10.9, U10.10
ICLK: J3.2, U2.7, U6.7, U8.7, U10.7
LOAD: D18.1, J2.2, R20.1, U1.9, U5.9, U7.9, U9.9
unnamed: D1.1, R1.2
unnamed: D2.1, R2.2
unnamed: D3.1, R3.2
unnamed: D4.1, R4.2
unnamed: D5.1, R5.2
unnamed: D6.1, R6.2
unnamed: D7.1, R7.2
unnamed: D8.1, R8.2
unnamed: D9.1, R9.2
unnamed: D10.1, R10.2
unnamed: D11.1, R11.2
unnamed: D12.1, R12.2
unnamed: D13.1, R13.2
unnamed: D14.1, R14.2
unnamed: D15.1, R15.2
unnamed: D16.1, R16.2
unnamed: D17.2, R17.2
unnamed: D18.2, R19.2
unnamed: D19.1, R21.2
unnamed: U1.15, U5.10
unnamed: U5.15, U7.10
unnamed: U7.15, U9.10
Q0: D1.2, U1.14, U2.11
Q1: D2.2, U1.13, U2.12
Q2: D3.2, U1.12, U2.13
Q3: D4.2, U1.11, U2.14
Q4: D5.2, U5.14, U6.11
Q5: D6.2, U5.13, U6.12
Q6: D7.2, U5.12, U6.13
Q7: D8.2, U5.11, U6.14
Q8: D9.2, U7.14, U8.11
Q9: D10.2, U7.13, U8.12
Q10: D11.2, U7.12, U8.13
Q11: D12.2, U7.11, U8.14
Q12: D13.2, U9.14, U10.11
Q13: D14.2, U9.13, U10.12
Q14: D15.2, U9.12, U10.13
Q15: D16.2, U9.11, U10.14
RST: J3.3, R24.2, U2.15, U6.15, U8.15, U10.15
UP: D19.2, J2.3, R22.1, U1.7, U5.7, U7.7, U9.7
VCC: C1.1, C2.1, C3.1, C4.1, C5.1, C6.1, C7.1, C8.1, C9.1, J4.3, J4.4, R17.1, R18.2, R19.1, R20.2, R23.1, U1.10, U1.16, U2.16, U5.16, U6.16, U7.16, U8.16, U9.16, U10.16
~RST~: J3.4, R23.2, U1.1, U5.1, U7.1, U9.1

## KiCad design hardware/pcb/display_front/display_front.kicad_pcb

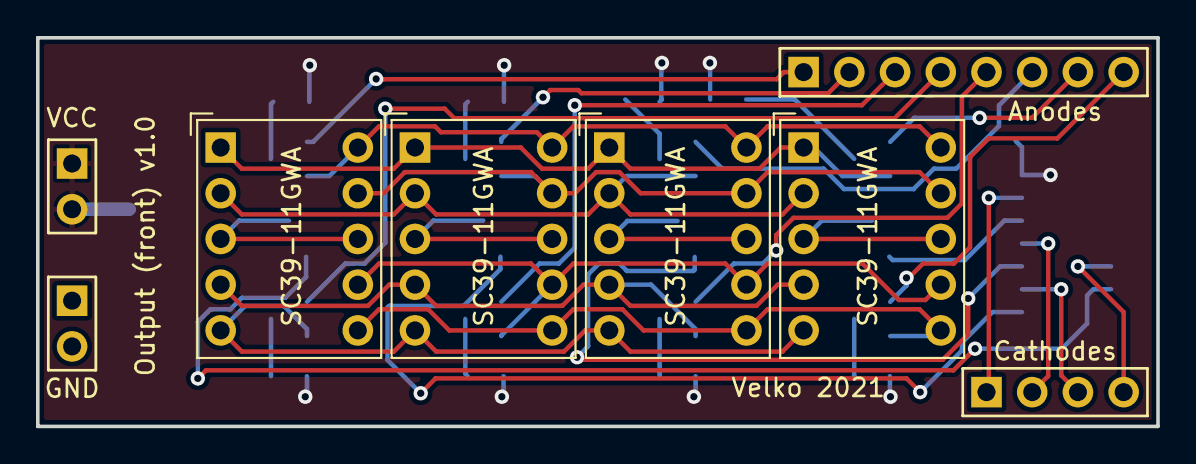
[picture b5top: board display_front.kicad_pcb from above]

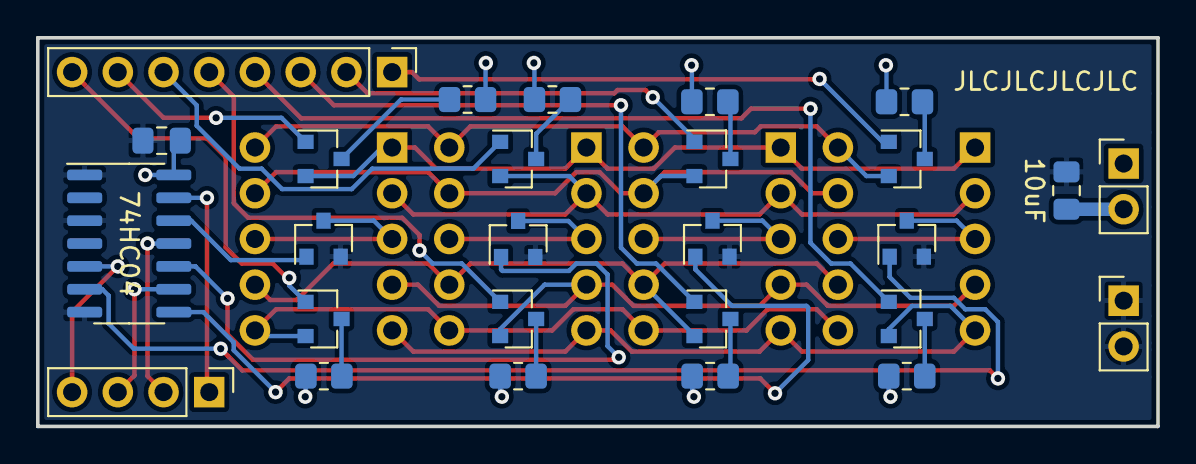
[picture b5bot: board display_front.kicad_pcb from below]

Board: 2 copper layers, 62.2 x 21.6 mm, 31 parts (27 on the bottom side), 38 nets.

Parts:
C9: 100nF; C_0805_2012Metric_Pad1.18x1.45mm_HandSolder
C10: 10uF; C_0805_2012Metric_Pad1.18x1.45mm_HandSolder
J5: Anodes; PinHeader_1x08_P2.54mm_Vertical
J6: Cathodes; PinHeader_1x04_P2.54mm_Vertical
J9: VCC; PinHeader_1x02_P2.54mm_Vertical
J10: GND; PinHeader_1x02_P2.54mm_Vertical
Q1, Q2, Q3, Q4, Q5, Q6, Q7, Q8, Q9, Q10, Q11, Q12: Q_NMOS_GSD; SOT-23
R1, R2, R3, R4, R5, R6, R7, R8: 100; R_0805_2012Metric_Pad1.20x1.40mm_HandSolder
U1: 74HC04; SOIC-14_3.9x8.7mm_P1.27mm
U2, U3, U4, U5: SC39-11GWA; Sx39-1xxxxx

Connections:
A: Q2.2, U2.10, U3.10, U4.10, U5.10
B: Q5.2, U2.9, U3.9, U4.9, U5.9
C: Q4.2, U2.7, U3.7, U4.7, U5.7
CA0: J6.1, U1.13
CA1: J6.2, U1.11
CA2: J6.3, U1.9
CA3: J6.4, U1.5
D: Q3.2, U2.5, U3.5, U4.5, U5.5
DA: J5.1, Q2.1
DB: J5.2, Q5.1
DC: J5.3, Q4.1
DD: J5.4, Q3.1
DDP: J5.8, Q12.1
DE: J5.5, Q7.1
DF: J5.6, Q9.1
DG: J5.7, Q10.1
DP: Q12.2, U2.6, U3.6, U4.6, U5.6
E: Q7.2, U2.4, U3.4, U4.4, U5.4
F: Q9.2, U2.2, U3.2, U4.2, U5.2
G: Q10.2, U2.1, U3.1, U4.1, U5.1
GND: C9.2, C10.2, J10.1, J10.2, Q1.2, Q6.2, Q8.2, Q11.2, U1.1, U1.3, U1.7
unnamed: Q1.1, U1.6
unnamed: Q1.3, U2.3, U2.8
unnamed: Q2.3, R1.2
unnamed: Q3.3, R4.2
unnamed: Q4.3, R3.2
unnamed: Q5.3, R2.2
unnamed: Q6.1, U1.8
unnamed: Q6.3, U3.3, U3.8
unnamed: Q7.3, R5.2
unnamed: Q8.1, U1.10
unnamed: Q8.3, U4.3, U4.8
unnamed: Q9.3, R6.2
unnamed: Q10.3, R7.2
unnamed: Q11.1, U1.12
unnamed: Q11.3, U5.3, U5.8
unnamed: Q12.3, R8.2
VCC: C9.1, C10.1, J9.1, J9.2, R1.1, R2.1, R3.1, R4.1, R5.1, R6.1, R7.1, R8.1, U1.14

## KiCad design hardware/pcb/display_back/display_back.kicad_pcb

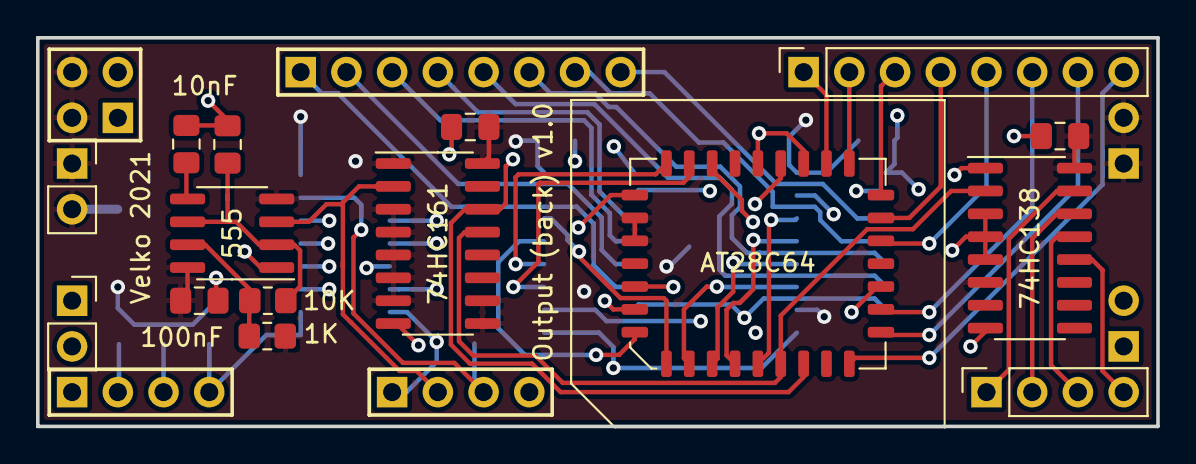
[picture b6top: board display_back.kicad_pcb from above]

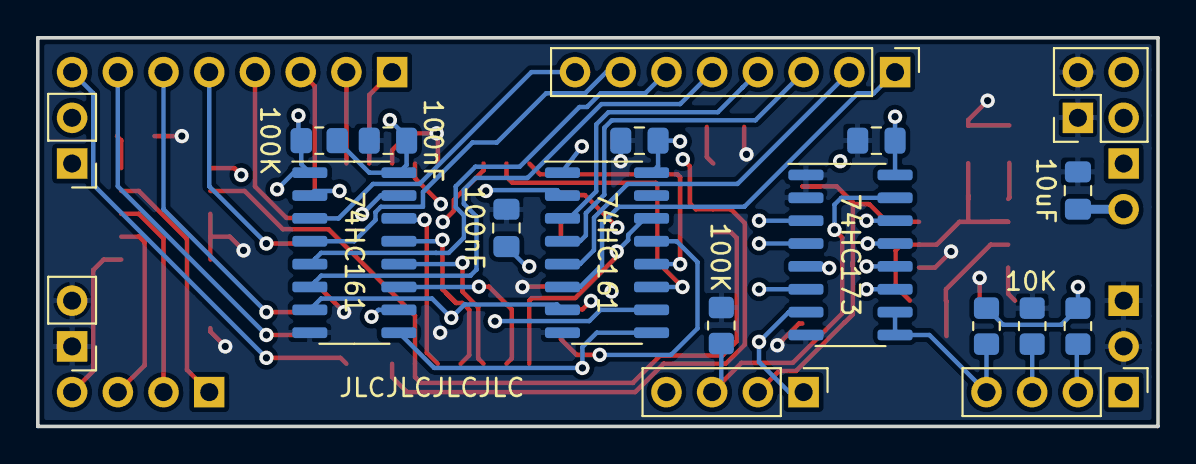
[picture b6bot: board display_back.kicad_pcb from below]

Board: 4 copper layers, 62.2 x 21.6 mm, 34 parts (19 on the bottom side), 47 nets.

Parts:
C1, C2: 10nF; C_0805_2012Metric_Pad1.18x1.45mm_HandSolder
C3, C4, C5, C6, C7, C8, C9: 100nF; C_0805_2012Metric_Pad1.18x1.45mm_HandSolder
C10: 10uF; C_0805_2012Metric_Pad1.18x1.45mm_HandSolder
J1: Conn_01x08_Male; PinHeader_1x08_P2.54mm_Vertical
J2, J3: Conn_01x04_Male; PinHeader_1x04_P2.54mm_Vertical
J4: Conn_01x04_Male; PinHeader_2x02_P2.54mm_Vertical
J5: DISP_ANODES; PinSocket_1x08_P2.54mm_Vertical
J6: DISP_CATHODES; PinSocket_1x04_P2.54mm_Vertical
J7: AUX_VCC; PinHeader_1x02_P2.54mm_Vertical
J8: AUX_GND; PinHeader_1x02_P2.54mm_Vertical
J9: VCC_OUT; PinSocket_1x02_P2.54mm_Vertical
J10: GND_OUT; PinSocket_1x02_P2.54mm_Vertical
R1: 1K; R_0805_2012Metric_Pad1.20x1.40mm_HandSolder
R2, R3, R4, R6: 10K; R_0805_2012Metric_Pad1.20x1.40mm_HandSolder
R5, R7: 100K; R_0805_2012Metric_Pad1.20x1.40mm_HandSolder
U1: AT28C64; PLCC-32_SMD-Socket
U2, U3, U4: 74HC161; SOIC-16_3.9x9.9mm_P1.27mm
U5: 74HC138; SOIC-16_3.9x9.9mm_P1.27mm
U6: 74HC173; SOIC-16_3.9x9.9mm_P1.27mm
U7: 555; SOIC-8_3.9x4.9mm_P1.27mm

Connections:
/CA0: J6.1, U5.15
/CA1: J6.2, U5.14
/CA2: J6.3, U5.13
/CA3: J6.4, U5.12
/DA0: J5.8, U1.13
/DA1: J5.7, U1.14
/DA2: J5.6, U1.15
/DA3: J5.5, U1.18
/DA4: J5.4, U1.19
/DA5: J5.3, U1.20
/DA6: J5.2, U1.21
/DA7: J5.1, U1.22
/M0: U1.24, U6.3
/M1: U1.27, U6.4
/M2: U1.3, U6.5
/M3: U1.30, U6.6
/MP_A0: U1.11, U2.14, U5.1
/MP_A1: U1.10, U2.13, U5.2
/V_A0: U1.9, U3.14
/V_A1: U1.8, U3.13
/V_A2: U1.7, U3.12
/V_A3: U1.6, U3.11
/V_A4: U1.5, U4.14
/V_A5: U1.4, U4.13
/V_A6: U1.29, U4.12
/V_A7: U1.28, U4.11
BUS0: J1.8, U3.3, U6.14
BUS1: J1.7, U3.4, U6.13
BUS2: J1.6, U3.5, U6.12
BUS3: J1.5, U3.6, U6.11
BUS4: J1.4, U4.3
BUS5: J1.3, U4.4
BUS6: J1.2, U4.5
BUS7: J1.1, U4.6
CLK: J3.1, U3.2, U4.2, U6.7
CLK_O: J3.2, U2.2, U7.3
COUNT: J2.3, R6.1, U3.7, U4.7
GND: C1.2, C2.2, C3.2, C4.2, C5.2, C6.2, C7.2, C8.2, C9.2, C10.2, J4.1, J4.2, J8.1, J8.2, J10.1, J10.2, R6.2, R7.2, U1.2, U1.16, U1.23, U1.25, U2.8, U3.8, U4.8, U5.3, U5.4, U5.5, U5.8, U6.1, U6.2, U6.8, U7.1
unnamed: C1.1, U7.5
unnamed: C2.1, R2.2, U7.2, U7.6
unnamed: R1.2, R2.1, U7.7
unnamed: U3.15, U4.10
RESET: J3.3, R7.1, U6.15
VCC: C3.1, C4.1, C5.1, C6.1, C7.1, C8.1, C9.1, C10.1, J4.3, J4.4, J7.1, J7.2, J9.1, J9.2, R1.1, R3.2, R4.2, R5.2, U1.31, U1.32, U2.1, U2.3, U2.4, U2.5, U2.6, U2.7, U2.9, U2.10, U2.16, U3.10, U3.16, U4.16, U5.6, U5.16, U6.16, U7.4, U7.8
~LOAD_M~: J2.4, R4.1, U6.9, U6.10
~LOAD~: J2.2, R3.1, U3.9, U4.9
~RESET~: J3.4, R5.1, U3.1, U4.1
